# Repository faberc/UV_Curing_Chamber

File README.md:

# UV Curing Chamber

This is a chamber for UV curing resin 3D prints for the Electronics Prototyping Lab at Portland State University.

To Do: Add section for photos here.

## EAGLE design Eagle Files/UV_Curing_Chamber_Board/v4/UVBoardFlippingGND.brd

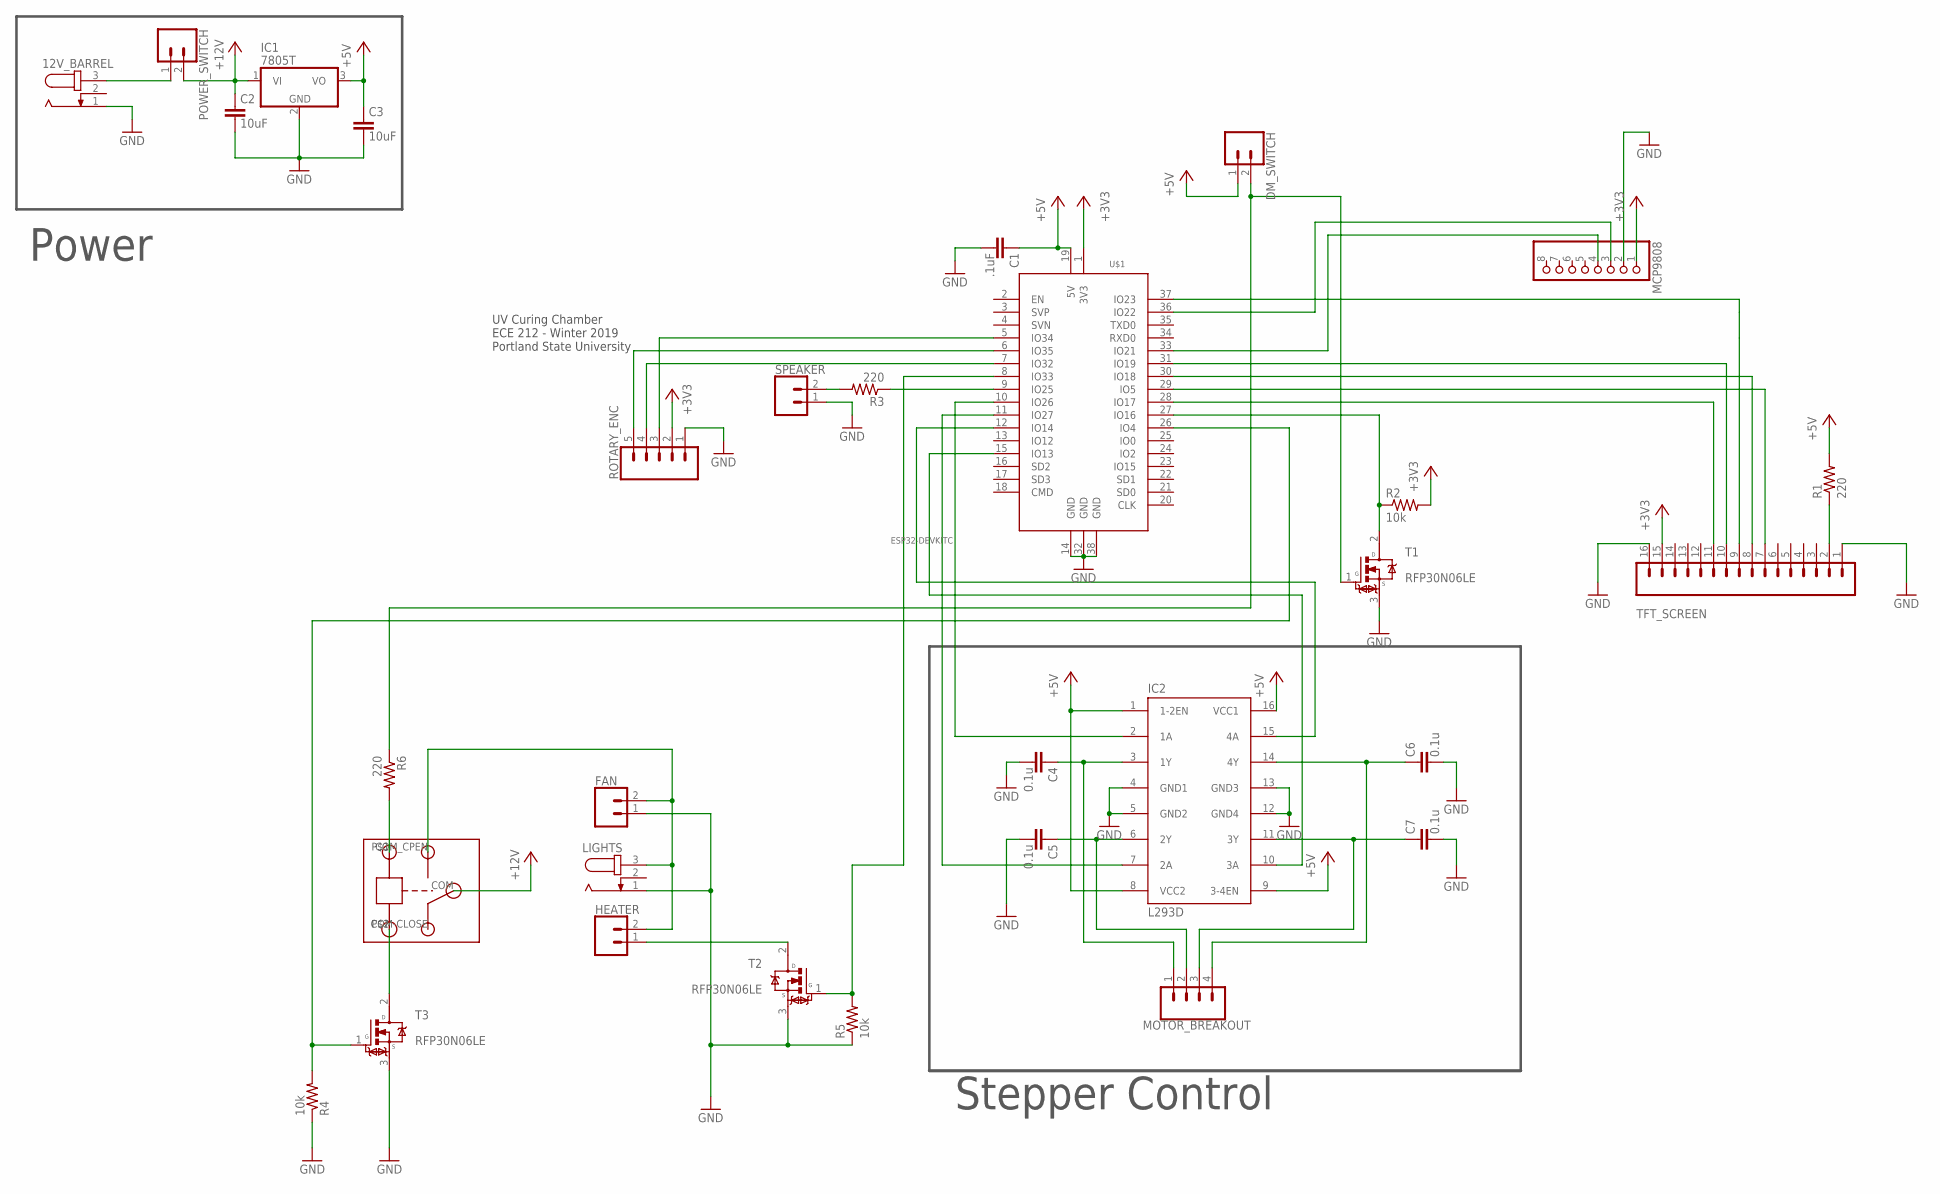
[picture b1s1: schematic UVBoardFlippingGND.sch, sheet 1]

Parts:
12V_BARREL: JACK-PLUG0; SPC4077
C1: .1uF; C0603
C2, C3: 10uF; C1206
C4, C5, C6, C7: 0.1u; C0603
DM_SWITCH: CONN_025MM; SCREWTERMINAL-5MM-2
FAN: CONN_025MM; SCREWTERMINAL-5MM-2
HEATER: CONN_025MM; SCREWTERMINAL-5MM-2
IC1: 7805T; TO220H
IC2: L293D; DIL16
LIGHTS: JACK-PLUG0; SPC4077
MCP9808: PINHD-1X8BIG; 1X08-BIG
MOTOR_BREAKOUT: CONN_04SCREW; SCREWTERMINAL-3.5MM-4
POWER_SWITCH: CONN_025MM; SCREWTERMINAL-5MM-2
R1, R3, R6: 220; R0805
R2, R4, R5: 10k; R0805
ROTARY_ENC: CONN_05; 1X05
SPEAKER: CONN_025MM; SCREWTERMINAL-5MM-2
T1, T2, T3: RFP30N06LE; TRANS_RFP30N06LE
TFT_SCREEN: CONN_16; 1X16
U$1: ESP32DEVKITC; ESP32-DEVKITC
U$2: RELAY

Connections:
+3V3: MCP9808.1, R2.2, ROTARY_ENC.2, TFT_SCREEN.15, U$1.1 (3V3)
+5V: C1.1, C3.1, DM_SWITCH.1, IC1.3 (VO), IC2.1 (1-2EN), IC2.8 (VCC2), IC2.9 (3-4EN), IC2.16 (VCC1), R1.2, U$1.19 (5V)
ASDSFA: C2.1, IC1.1 (VI), POWER_SWITCH.2, U$2.COM
GND: 12V_BARREL.1, C1.2, C2.2, C3.2, C4.2, C5.2, C6.2, C7.2, FAN.1, IC1.2 (GND), IC2.4 (GND1), IC2.5 (GND2), IC2.12 (GND4), IC2.13 (GND3), LIGHTS.1, MCP9808.2, R4.1, R5.1, ROTARY_ENC.1, SPEAKER.1, T1.3 (S), T2.3 (S), T3.3 (S), TFT_SCREEN.1, TFT_SCREEN.16, U$1.14 (GND), U$1.32 (GND), U$1.38 (GND)
unnamed: TFT_SCREEN.9, U$1.37 (IO23)
unnamed: IC2.15 (4A), U$1.12 (IO14)
unnamed: 12V_BARREL.3, POWER_SWITCH.1
unnamed: HEATER.1, T2.2 (D)
unnamed: IC2.7 (2A), U$1.11 (IO27)
unnamed: R3.2, SPEAKER.2
unnamed: C5.1, IC2.6 (2Y), MOTOR_BREAKOUT.2
unnamed: DM_SWITCH.2, R6.1, T1.1 (G)
unnamed: R2.1, T1.2 (D), U$1.27 (IO16)
unnamed: MCP9808.3, U$1.36 (IO22)
unnamed: MCP9808.4, U$1.33 (IO21)
unnamed: IC2.2 (1A), U$1.10 (IO26)
unnamed: R5.2, T2.1 (G), U$1.8 (IO33)
unnamed: C4.1, IC2.3 (1Y), MOTOR_BREAKOUT.1
unnamed: R4.2, T3.1 (G), U$1.26 (IO4)
unnamed: R1.1, TFT_SCREEN.2
unnamed: ROTARY_ENC.3, U$1.5 (IO34)
unnamed: ROTARY_ENC.4, U$1.7 (IO32)
unnamed: ROTARY_ENC.5, U$1.6 (IO35)
unnamed: TFT_SCREEN.11, U$1.28 (IO17)
unnamed: TFT_SCREEN.10, U$1.31 (IO19)
unnamed: C7.1, IC2.11 (3Y), MOTOR_BREAKOUT.3
unnamed: TFT_SCREEN.8, U$1.30 (IO18)
unnamed: TFT_SCREEN.7, U$1.29 (IO5)
unnamed: R3.1, U$1.9 (IO25)
unnamed: C6.1, IC2.14 (4Y), MOTOR_BREAKOUT.4
unnamed: FAN.2, HEATER.2, LIGHTS.3, U$2.COM_CPEN (COM-OPEN)
unnamed: IC2.10 (3A), U$1.15 (IO13)
unnamed: T3.2 (D), U$2.P$2 (GND)
unnamed: R6.2, U$2.P$1 (IN)

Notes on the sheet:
UV Curing Chamber ECE 212 - Winter 2019 Portland State University
Stepper Control
Power

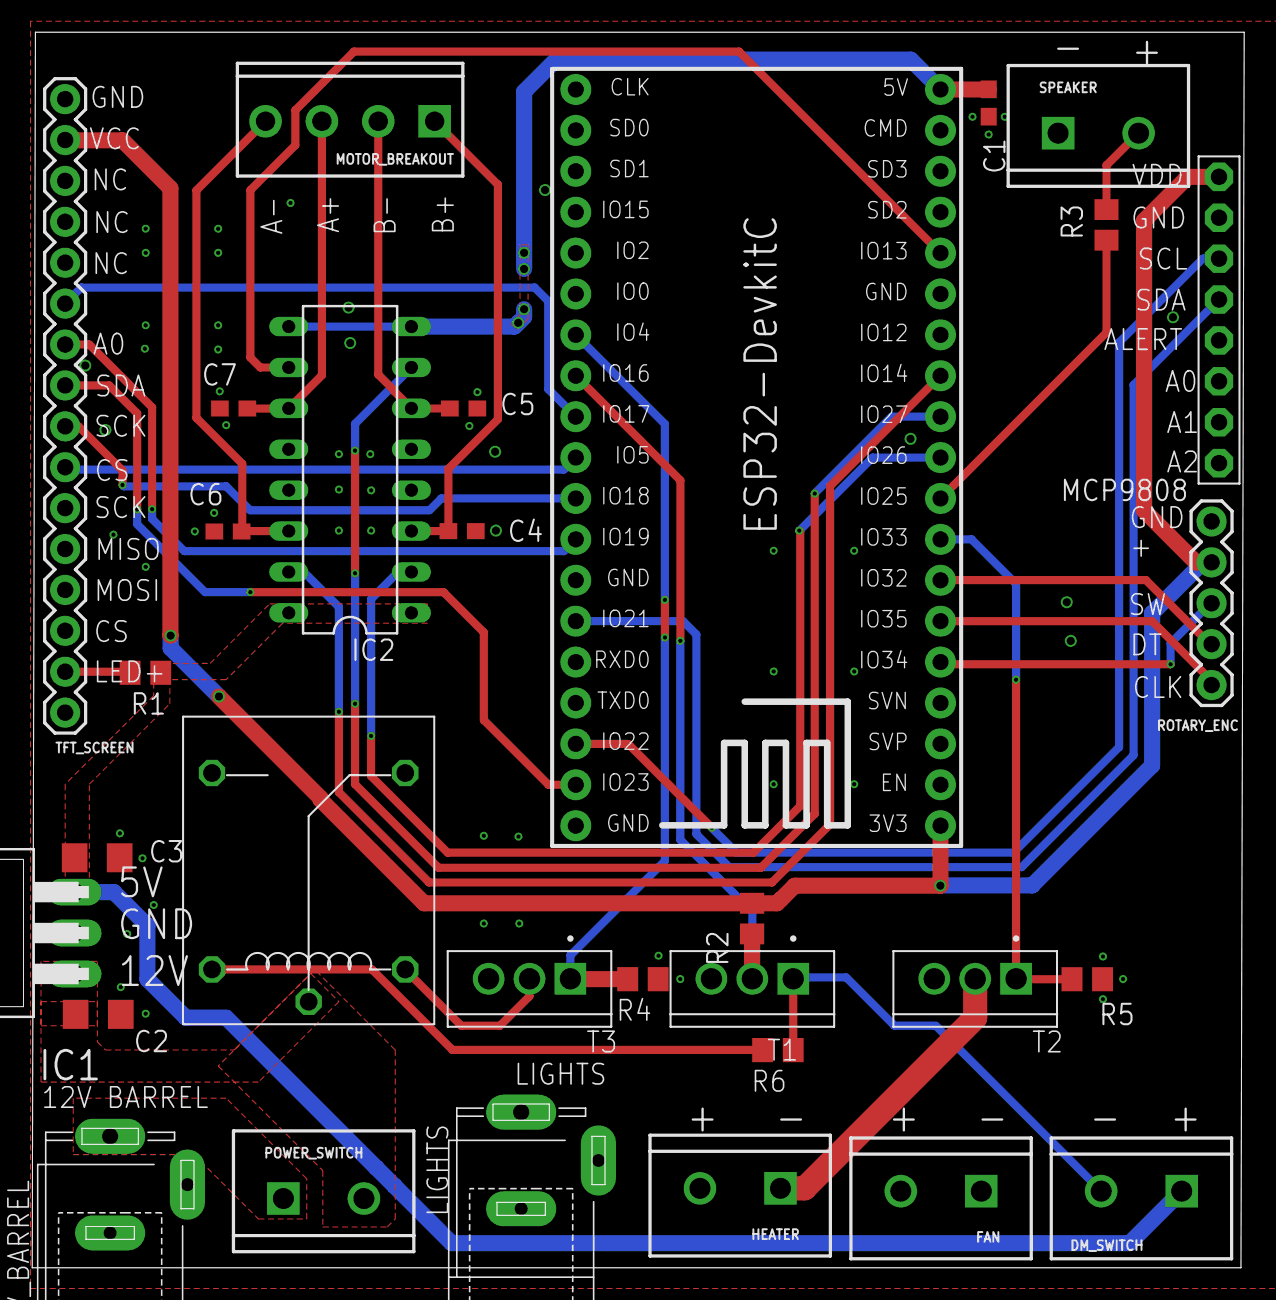
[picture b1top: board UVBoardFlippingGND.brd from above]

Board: 2 copper layers, 75.3 x 76.7 mm, 31 parts (0 on the bottom side), 34 nets.

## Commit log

2019-11-01 v4 board start
2019-11-01 Updated V4
2019-11-06 V4 board now has relay circuit on board.
2019-11-22 SMD revisions for the PCB
2020-01-16 Added comments about switching out the transistors in the V4 schematic.
2020-01-18 changed notes layers

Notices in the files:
parts and their libraries:
SparkFun-Connectors: Licensing: Creative Commons ShareAlike 4.0 International - https://creativecommons.org/licenses/by-sa/4.0
